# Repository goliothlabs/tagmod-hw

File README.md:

# TagMod

TagMod is a small companion/adapter PCB ("mod") for a SEGGER J-Link debug
probe. It plugs into the J-Link's 20-pin ARM JTAG/SWD header (J101) and
re-fans the signals out to a target-side 10-pin header (J103) plus a
dedicated UART header (J1), and it can supply the target with a
resistor-selectable 1.8 V / 3.3 V rail generated on-board from a USB-C
5 V input.

The earlier working name for this design was `jlink-uart-mod` (see
`output/jlink-uart-mod-a-202503092059.zip`); the project files were
renamed to match this repository in commit `7d403b9`.

## What it is for

Bringing up and debugging small Golioth hardware designs that expose a
compact 10-pin SWD + UART debug connection (e.g. via a Tag-Connect-style
cable — note the `TC TX` / `TC RX` silkscreen) instead of a full 20-pin
ARM header. One board carries SWD, target UART (through the J-Link's
built-in VCOM), and target power between the J-Link and the device under
test. Carries a 5 mm Golioth logo footprint (`footprints.pretty/the_golioth_5mm`).

## Hardware summary

Derived from `TagMod.kicad_sch` / `TagMod.kicad_pcb` (no other docs exist):

| Ref  | Part / footprint | Function |
|------|------------------|----------|
| J101 | 2x10 2.54 mm pin header (Conn_ARM_JTAG_SWD_20) | Input from J-Link 20-pin ARM JTAG/SWD header (SWDIO, SWCLK, RESET_N, TRST, RTCK, TDO/SWO, J-Link UART TX/RX) |
| J103 | 2x05 2.54 mm pin header (Conn_ARM_JTAG_SWD_10) | Target-side SWD output (10-pin ARM Cortex / Tag-Connect-ribbon-compatible) |
| J1   | 1x03 2.54 mm pin header | Target UART breakout (TARGET_TX / TARGET_RX / GND) |
| U4   | GT-USB-7010ASV USB-C connector | 5 V input only (CC1/CC2 terminated with 5.1 kΩ; D+/D-/SBU unconnected) |
| U1   | AMS1117-ADJ (SOT-89) | Adjustable LDO generating the VOUT target rail from the 5 V input |
| D1, D2 | CUS10S30 Schottky (SOD-323) | Rail steering / protection |
| 2x LED (0603, red) | — | `Input Power` and `Output Power` indicators (silkscreen) |
| TP101-103 | 2.0 mm test points | Bench access |
| —    | the_golioth_5mm | Golioth logo silkscreen artwork |

Signal flow (net names): `JLINK_TX`/`JLINK_RX` (J-Link VCOM) are crossed to
`TARGET_TX`/`TARGET_RX`; `SWDIO`, `SWCLK`, `RESET_N` route J101 to J103.
The `ADJ`/`VOUT` divider (6.1 kΩ reference with 2.7 kΩ / 10 kΩ options,
selected with 0-ohm jumpers) gives nominal **1.8 V or 3.3 V** target
supply, matching the `1V8` / `3V3` silkscreen selectors.

## Repository contents

- `TagMod.kicad_pro`, `TagMod.kicad_sch`, `TagMod.kicad_pcb`, `TagMod.kicad_prl` — KiCad 9.0 project (single-sheet schematic, 2-layer PCB)
- `footprints.pretty/the_golioth_5mm.kicad_mod` — local Golioth logo footprint
- `fp-lib-table`, `sym-lib-table` — library tables (note: several symbols/footprints come from an `easyeda2kicad` library that is NOT in this repo; see Known gaps)
- `output/gerber/` — rev B fabrication outputs (gerbers + drill)
- `output/jlink-uart-mod-a-202503092059.zip` — gerber bundle from the earlier rev-A-era `jlink-uart-mod` design (March 2025)
- `TagMod-backups/` — 9 KiCad auto-backup zips (tracked in git; should not be)
- `input/`, `input/3d/` — tracked only via stray `.DS_Store` files; actual contents unknown [UNKNOWN]

## Status (October 2026)

- 4 commits, all 2026-01-21 to 2026-01-23. No activity since.
- Rev A: initial board had the J-Link UART TX/RX flipped (commit `920f7ca`).
- Rev B: TX/RX swapped, renamed to TagMod, "passes DRC, ready for fab"
  (commit `7862415`, 2026-01-22). Gerbers in `output/gerber/` are the
  rev B outputs.
- Whether rev B was ever fabricated, assembled, or electrically validated:
  [UNKNOWN].
- Design tool: KiCad 9.0 (schematic format 20250114, PCB format 20241229).

## Known gaps (pre-open-sourcing checklist)

- **No LICENSE file.** A license (e.g. CERN-OHL, Apache-2.0, MIT) must be
  chosen and added before publishing.
- **Tracked junk:** `.DS_Store` (x3: root, `footprints.pretty/`, `input/3d/`),
  `fp-info-cache` (KiCad cache), `~TagMod.kicad_pcb.lck` (lock file),
  `TagMod-backups/*.zip` (9 auto-backups), and `output/*`. The `.gitignore`
  added in the final commit (`45dc6e3`) already covers `*.zip`,
  `/*-backup/*`, `output/*`, and `*.lck`, but the files were never removed
  from the index (`git rm --cached` needed).
- **No schematic/PCB title-block metadata** (no title, author, revision, or
  date fields set in the KiCad files) — this README is the only description
  of the project.
- **External symbol/footprint dependency:** the design uses an
  `easyeda2kicad` library (AMS1117, USB-C connector, LEDs, diodes, caps)
  that is not vendored into this repo; the schematic will not render
  correctly on a fresh checkout without it.
- **Stale artifact:** `output/jlink-uart-mod-a-202503092059.zip` predates
  this repository (March 2025) and reflects the old project name/rev A.
- **No BOM, assembly drawing, or fabrication notes.**
- Secrets sweep (2026-10): clean. No credentials, keys, or personal emails
  in any tracked file. (The two 24-hex strings in `fp-info-cache` are KiCad
  footprint-cache hashes, and `psk` matches are the Murata "TPSKA"
  resonator part name — both false positives.)

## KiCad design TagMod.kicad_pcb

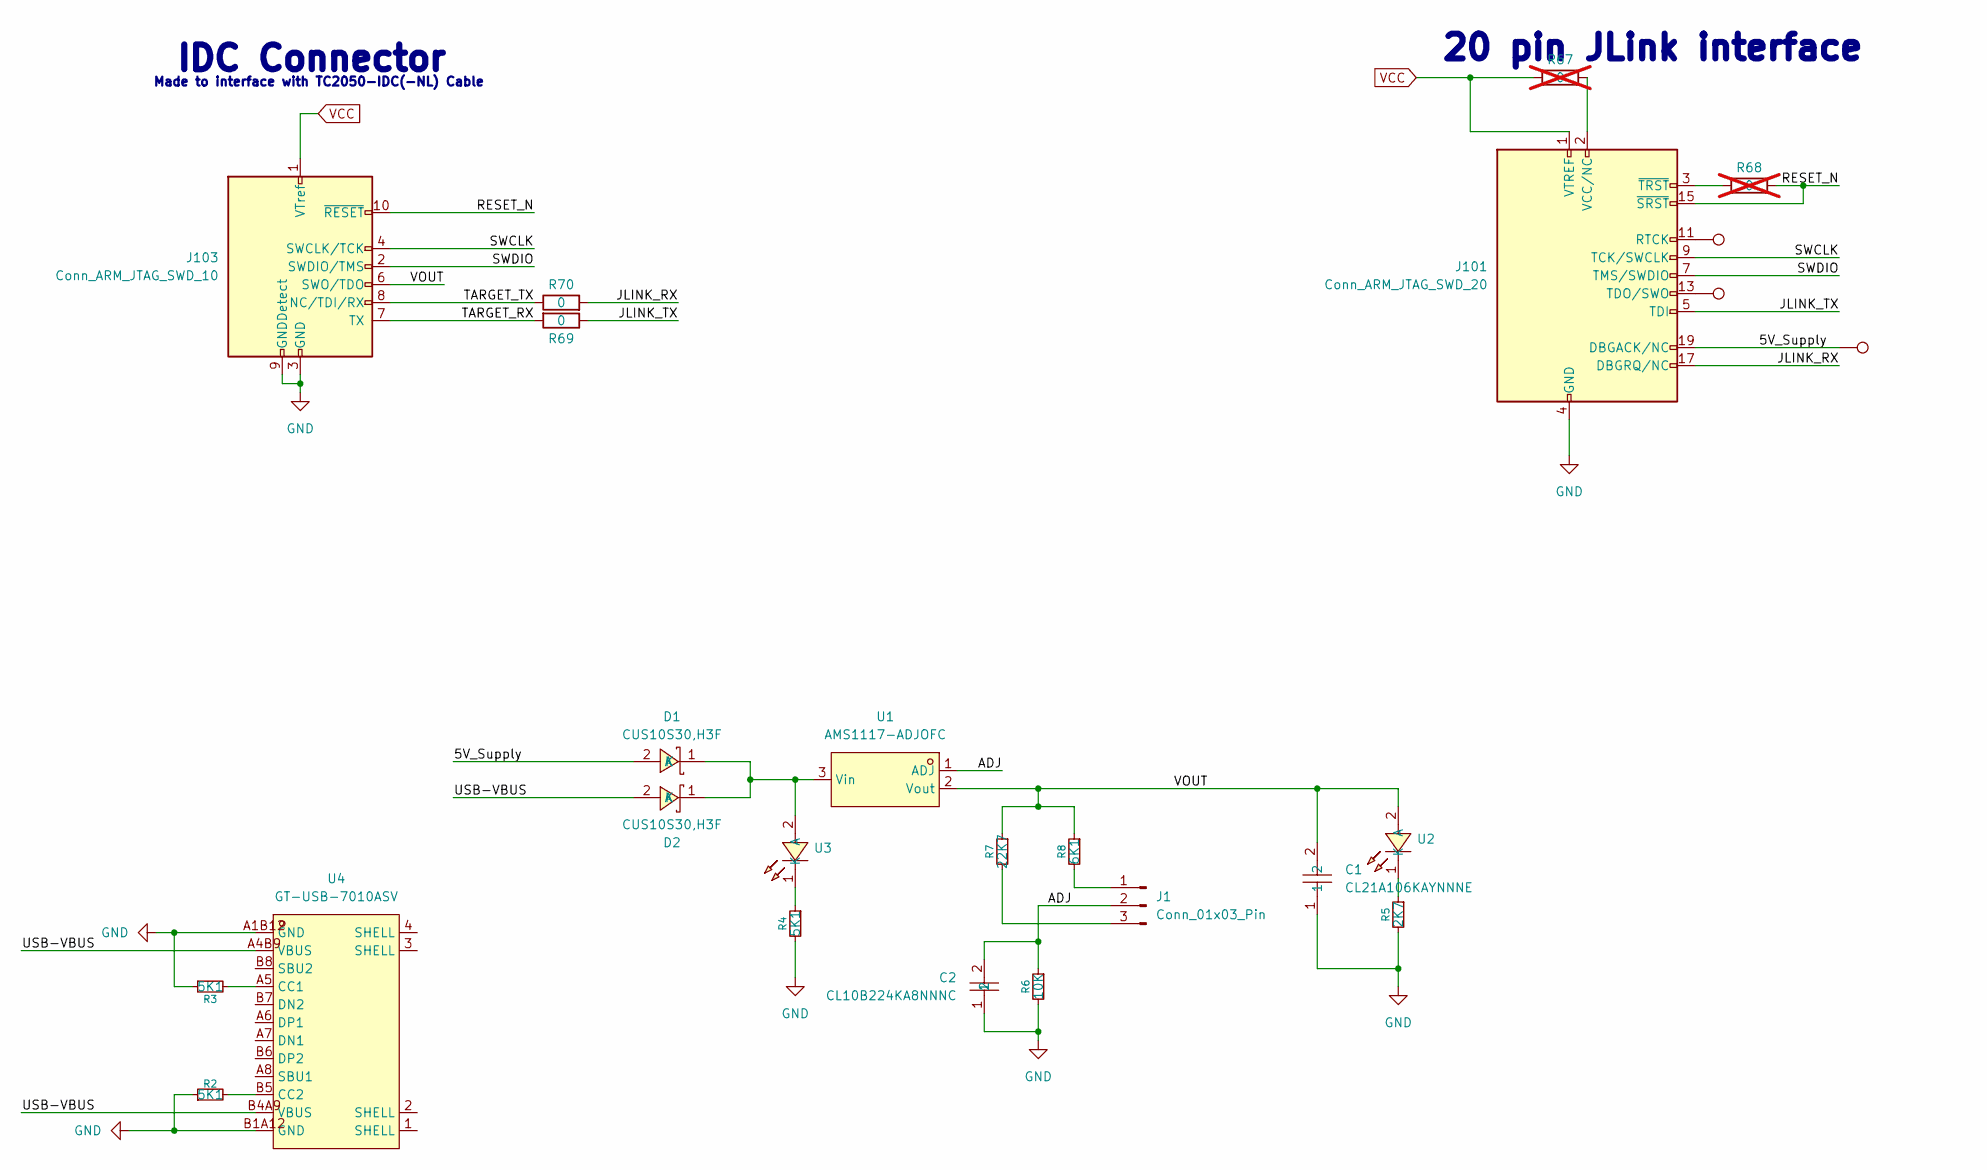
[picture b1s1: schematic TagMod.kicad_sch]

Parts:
C1: CL21A106KAYNNNE; C0805; LCSC Part C15850
C2: CL10B224KA8NNNC; C0603; LCSC Part C21120
D1, D2: CUS10S30,H3F; SOD-323_L1.8-W1.3-LS2.5-RD; LCSC Part C146335
J1: Conn_01x03_Pin; PinHeader_1x03_P2.54mm_Vertical
J101: Conn_ARM_JTAG_SWD_20; PinHeader_2x10_P2.54mm_Vertical
J103: Conn_ARM_JTAG_SWD_10; PinHeader_2x05_P2.54mm_Vertical
R2, R3, R4: 5K1; R_0603_1608Metric
R5: 2K7; R_0603_1608Metric
R6: 10K; R_0603_1608Metric
R7: 22K7; R_0603_1608Metric
R8: 6K1; R_0603_1608Metric
R67, R68: 0; R_0603_1608Metric; not fitted
R69, R70: 0; R_0603_1608Metric
TP101, TP102, TP103: TestPoint; TestPoint_Pad_2.0x2.0mm
U1: AMS1117-ADJOFC; SOT-89-3_L4.5-W2.5-P1.50-LS4.1-BR-1; LCSC Part C50313810
U2, U3: F.0603.00139/P2-0603R1TS2-06T-002; LED0603-RD; LCSC Part C7496820
U4: GT-USB-7010ASV; USB-C-SMD_G-SWITCH_GT-USB-7010ASV; LCSC Part C2988369

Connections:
/5V_Supply: D1.2 (A), J101.19 (DBGACK/NC), TP102.1
/ADJ: C2.2, J1.2, R6.1, U1.1 (ADJ)
/JLINK_RX: J101.17 (DBGRQ/NC), R70.2
/JLINK_TX: J101.5 (TDI), R69.1
/RESET_N: J101.15 (~SRST), J103.10 (~RESET), R68.1
/SWCLK: J101.9 (TCK/SWCLK), J103.4 (SWCLK/TCK)
/SWDIO: J101.7 (TMS/SWDIO), J103.2 (SWDIO/TMS)
/TARGET_RX: J103.7 (TX), R69.2
/TARGET_TX: J103.8 (NC/TDI/RX), R70.1
/USB-VBUS: D2.2 (A), U4.A4B9 (VBUS), U4.B4A9 (VBUS)
/VOUT: C1.2, J103.6 (SWO/TDO), R7.1, R8.1, U1.2 (Vout), U2.2 (A)
GND: C1.1, C2.1, J101.4 (GND), J101.6 (GND), J101.8 (GND), J101.10 (GND), J101.12 (GND), J101.14 (GND), J101.16 (GND), J101.18 (GND), J101.20 (GND), J103.3 (GND), J103.5 (GND), J103.9 (GNDDetect), R2.1, R3.1, R4.2, R5.2, R6.2, U4.A1B12 (GND), U4.B1A12 (GND)
unnamed: D1.1 (K), D2.1 (K), U1.3 (Vin), U3.2 (A)
unnamed: J1.1, R8.2
unnamed: J1.3, R7.2
unnamed: J101.11 (RTCK), TP101.1
unnamed: J101.13 (TDO/SWO), TP103.1
unnamed: J101.2 (VCC/NC), R67.1
unnamed: J101.3 (~TRST), R68.2
unnamed: R5.1, U2.1 (K)
unnamed: R4.1, U3.1 (K)
unnamed: R3.2, U4.A5 (CC1)
unnamed: R2.2, U4.B5 (CC2)
VCC: J101.1 (VTREF), J103.1 (VTref), R67.2

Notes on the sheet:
IDC Connector
20 pin JLink interface
Made to interface with TC2050-IDC(-NL) Cable

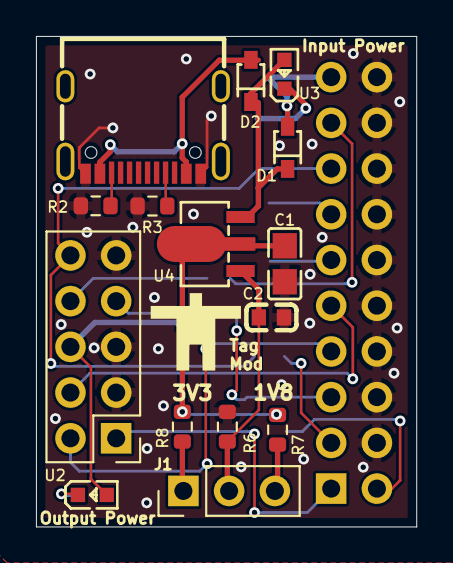
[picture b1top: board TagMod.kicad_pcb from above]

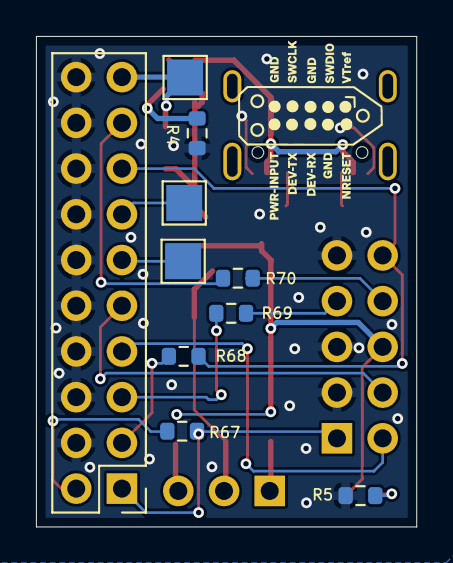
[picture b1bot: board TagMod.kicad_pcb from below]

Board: 2 copper layers, 21.1 x 27.2 mm, 25 parts (10 on the bottom side), 24 nets.

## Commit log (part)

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2026-01-22 initial commit with rev A board (tx/rx flipped)
2026-01-22 rename project files to match repo and swap tx/rx
2026-01-22 rev b passes drc, ready for fab
2026-01-23 add gitignore
2026-01-23 rev b all checks passed
